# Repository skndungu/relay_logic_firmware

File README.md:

# Relay Logic Firmware
The repo contains all the firmware codes for the project and instructions on how to load them to the hardware
  <br/>

## What's fisrt needed
1) Set up the IDE, for this application you will need to down the Arduino ide [here](https://www.arduino.cc/en/software) if you don't have it already installed for your distributions
2) Once downloaded and proceed to the next instructions

## Download the Files :arrow_down_small:
3)  Download all the files on the `Code`:arrow_down_small: on this platform, In your downloads you will get the a folder :file_folder:  `relay_logic_firmware
-master` this will have all the codes and related libraries.
## Burning bootload to the MCU :fire:
## Note: DO THIS ON A WINDOWS OPERATING SYSTEM!!!
4) Do this on older version of arduino particularly version 1.6.0 grab the software [here](https://www.arduino.cc/en/Main/OldSoftwareReleases)
5) Once you have the setup to burn the bootloader please follow this tutorial [here](https://www.youtube.com/watch?v=Kh4iZb2YTT8&t=337s)
6) You need to have a functional Arduino Nano with you - just buy one locally as it's used in the process of bootloading
 
# Uploading the codes  :arrow_up:

You can buy the USBASP from here :link: [buy usbasp](https://aliexpress.ru/af/USBASP-USBISP-AVR-Programmer-USB.html?catId=0&d=y&aff_platform=portals-tool&initiative_id=SB_20201020044645&origin=n&sk=_9JHld5&aff_trace_key=4b1704d992da43b586041dfb7cd31d7e-1606574782769-00350-_9JHld5&SearchText=USBASP%2BUSBISP%2BAVR%2BProgrammer%2BUSB&terminal_id=351d58321dfa473cb106b58978d7c19c)
or here 
 :link: [buy usbasp](https://aliexpress.ru/item/32649685244.html?spm=a2g0o.productlist.0.0.22e26eaf2mIeLt&algo_pvid=b6506204-320d-4244-9d76-c7a1c32c5ee5&algo_expid=b6506204-320d-4244-9d76-c7a1c32c5ee5-16&btsid=0b8b036a16065747853274219e2939&ws_ab_test=searchweb0_0,searchweb201602_,searchweb201603_)

1) Insert the ISP programmer cable socket onto ISP header. ...
2) Open Arduino IDE software. ...
3) Next, call out the source code. ...
4) Select “USBasp” from the Tools > Programmer menu.
5) Select “Upload using Programmer” from the File menu.

<h3> upload the code snapshot </h3> see the screenshot

</img> 
You can also explore more from the following tutorial :link:[How to Use USBasp Programmer with Arduino Boards](https://www.youtube.com/watch?v=ToKerwRR-70)

## Debugging 
9) To see the serial data as sent or received from either of the boards we can use the FTDI programmer or any USB to TTL converter so that you can have access to a serial port. Check out the headers on the board for uart communications

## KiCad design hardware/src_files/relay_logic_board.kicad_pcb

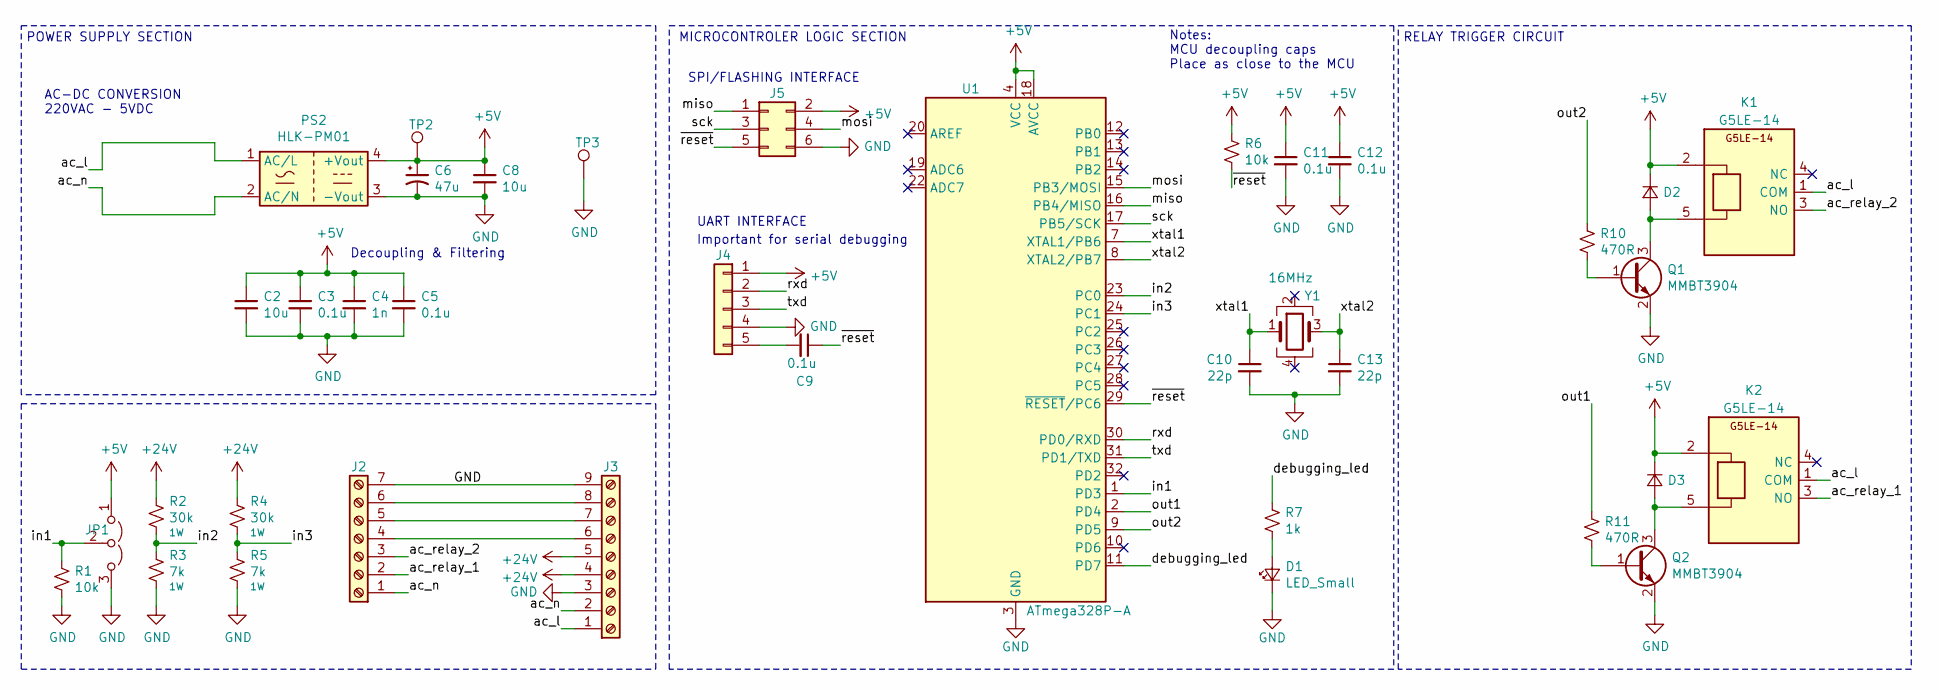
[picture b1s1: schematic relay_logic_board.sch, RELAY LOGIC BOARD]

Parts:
C2, C8: 10u; C_0603_1608Metric
C3, C5, C9, C11, C12: 0.1u; C_0603_1608Metric
C4: 1n; C_0603_1608Metric
C6: 47u; CP_Elec_4x5.3
C10, C13: 22p; C_0603_1608Metric
D1: LED_Small; LED_0603_1608Metric_Pad1.05x0.95mm_HandSolder
D2, D3: D_Small; D_SOD-123
J2: Screw_Terminal_01x07; TerminalBlock_4Ucon_1x07_P3.50mm_Horizontal
J3: Screw_Terminal_01x09; TerminalBlock_4Ucon_1x09_P3.50mm_Horizontal
J4: Conn_01x05; PinHeader_1x05_P2.54mm_Vertical
J5: Conn_02x03_Odd_Even; PinHeader_2x03_P2.54mm_Vertical
JP1: Jumper_3_Open; PinHeader_1x03_P2.54mm_Vertical
K1, K2: G5LE-14; Mfr# G5LE-14-DC5
PS2: HLK-PM01; Converter_ACDC_HiLink_HLK-PMxx
Q1, Q2: MMBT3904; SOT-23
R1, R6: 10k; R_0603_1608Metric
R2, R4: 30k; R_2512_6332Metric; Mfr# CR2512J30K0E04Z
R3, R5: 7k; R_2512_6332Metric; Mfr# AECR2512F1K00K9
R7: 1k; R_0603_1608Metric
R10, R11: 470R; R_0603_1608Metric
TP2, TP3: TestPoint; TestPoint_Pad_D0.9mm
U1: ATmega328P-A; TQFP-32_7x7mm_P0.8mm
Y1: 16MHz; Crystal_SMD_Abracon_ABM8G-4Pin_3.2x2.5mm

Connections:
+5V: C2.1, C3.1, C4.1, C5.1, C6.1, C8.1, C11.1, C12.1, D2.1 (K), D3.1 (K), J4.1, J5.2, JP1.1 (A), K1.2, K2.2, PS2.4 (+Vout), R6.2, TP2.1, U1.4 (VCC), U1.6 (VCC), U1.18 (AVCC)
+24V: J3.4, J3.5, R2.1, R4.1
/ac_l: J3.1, K1.1 (COM), K2.1 (COM), PS2.1 (AC/L)
/ac_n: J2.1, J3.2, PS2.2 (AC/N)
/ac_relay_1: J2.2, K2.3 (NO)
/ac_relay_2: J2.3, K1.3 (NO)
/debugging_led: R7.1, U1.11 (PD7)
/in1: JP1.2 (C), R1.2, U1.1 (PD3)
/in2: R2.2, R3.1, U1.23 (PC0)
/in3: R4.2, R5.1, U1.24 (PC1)
/miso: J5.1, U1.16 (PB4/MISO)
/mosi: J5.4, U1.15 (PB3/MOSI)
/out1: R11.1, U1.2 (PD4)
/out2: R10.1, U1.9 (PD5)
/rxd: J4.2, U1.30 (PD0/RXD)
/sck: J5.3, U1.17 (PB5/SCK)
/txd: J4.3, U1.31 (PD1/TXD)
/xtal1: C10.1, U1.7 (XTAL1/PB6), Y1.1
/xtal2: C13.1, U1.8 (XTAL2/PB7), Y1.3
/~reset: C9.1, J5.5, R6.1, U1.29 (~RESET~/PC6)
GND: C2.2, C3.2, C4.2, C5.2, C6.2, C8.2, C10.2, C11.2, C12.2, C13.2, D1.1 (K), J2.7, J3.3, J3.9, J4.4, J5.6, JP1.3 (B), PS2.3 (-Vout), Q1.2 (E), Q2.2 (E), R1.1, R3.2, R5.2, TP3.1, U1.3 (GND), U1.5 (GND), U1.21 (GND)
unnamed: C9.2, J4.5
unnamed: D1.2 (A), R7.2
unnamed: D2.2 (A), K1.5, Q1.3 (C)
unnamed: D3.2 (A), K2.5, Q2.3 (C)
unnamed: J2.4, J3.6
unnamed: J2.5, J3.7
unnamed: J2.6, J3.8
unnamed: Q1.1 (B), R10.2
unnamed: Q2.1 (B), R11.2

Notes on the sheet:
Notes: MCU decoupling caps Place as close to the MCU
UART INTERFACE
Important for serial debugging
SPI/FLASHING INTERFACE
MICROCONTROLER LOGIC SECTION
POWER SUPPLY SECTION
AC-DC CONVERSION 220VAC - 5VDC
Decoupling & Filtering
RELAY TRIGGER CIRCUIT

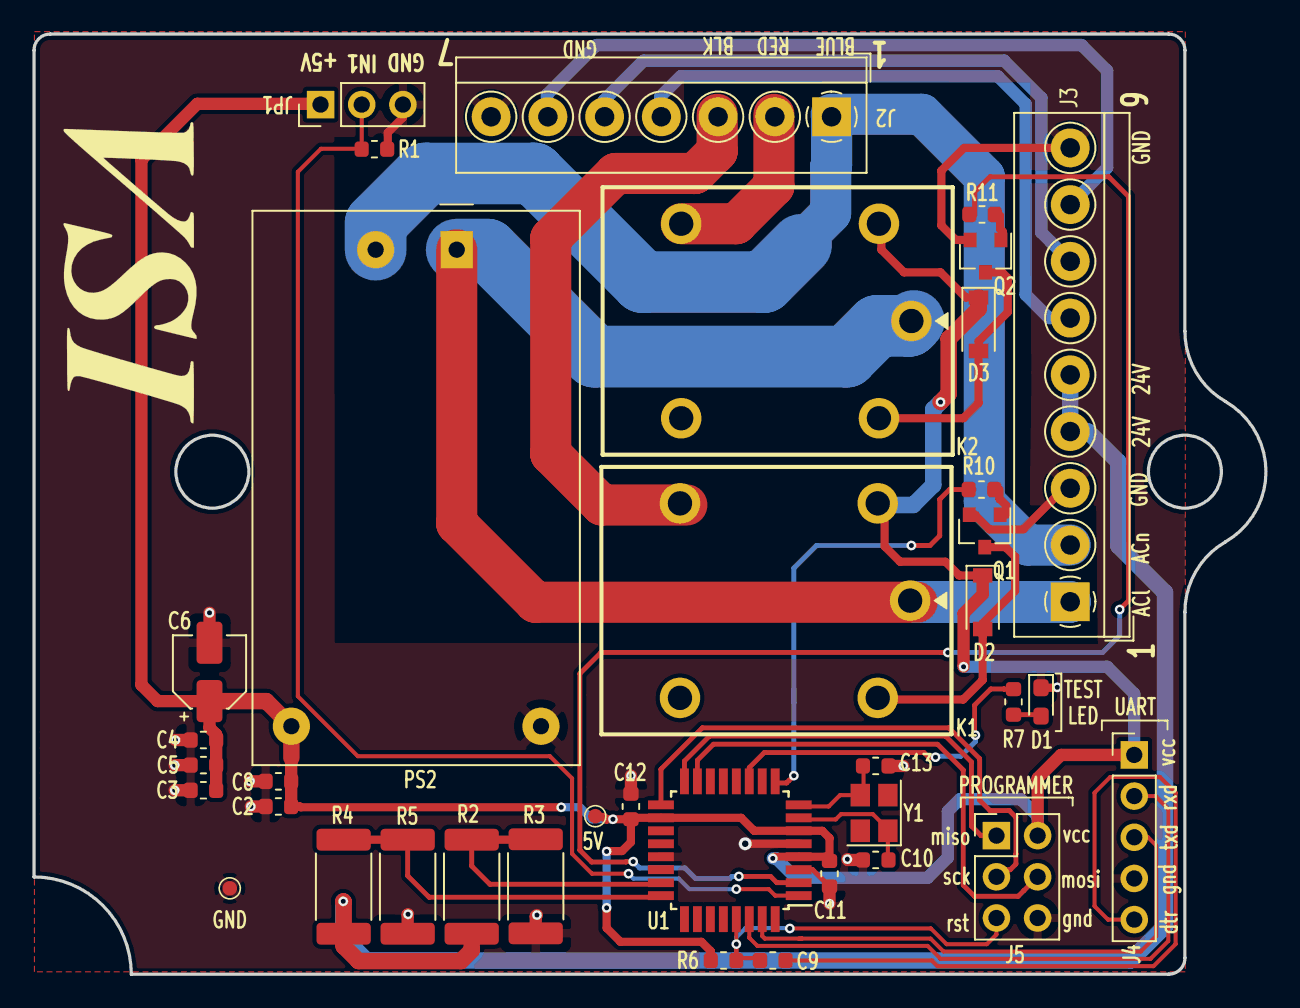
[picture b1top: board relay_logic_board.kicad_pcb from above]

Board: 2 copper layers, 76.0 x 58.0 mm, 37 parts (0 on the bottom side), 30 nets.

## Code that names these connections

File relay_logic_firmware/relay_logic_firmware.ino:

/*
 * TITLE: RELAY LOGIC FIRMWARE
 * 
 * AUTHOR: SIMON
 *
 * DATE: SEP, 23 2021
 * 
 */

#define in1 3  // input terminal
#define in2 A0 // input terminal
#define in3 A1 // input terminal
#define out1 4  // relay triggers
#define out2 5 // relay triggers

#define debugging_led 7 // led on the board for debugging 

int in1_state = 0;
int in2_state = 0;
int in3_state = 0;

boolean development = true;

void setup() {
  if(development){
  	  Serial.begin(9600);
  	  Serial.println("Relay Logic Test!");
  }
  pinMode(debugging_led, OUTPUT);
  pinMode(out1, OUTPUT);
  pinMode(out2, OUTPUT);
  pinMode(in1, INPUT);

  test_led();
}

void loop() {
 execute();
}

void take_reading(){
in1_state = digitalRead(in1);
in2_state = analogRead(in2);
in3_state = analogRead(in3);

if(in2_state > 400){ // takes an analog value if greater that 400 means we have an input voltage
	in2_state = 1;
} else{
	in2_state = 0;
}

if(in3_state > 400){
  in3_state = 1;
} else{
	in3_state = 0;
}

Serial.print("in1: ");
Serial.println(in1_state);
Serial.print("in2: ");
Serial.println(in2_state);
Serial.print("in3: ");
Serial.println(in3_state);

Serial.println("");

}

void execute(){
	if(in1 == 0 && in2 == 0 && in3 == 0){
		digitalWrite(out1, LOW);
		digitalWrite(out2, LOW);
	}
	if(in1 == 0 && in2 == 0 && in3 == 1){
		digitalWrite(out1, LOW);
		digitalWrite(out2, HIGH);
	}
	if(in1 == 0 && in2 == 1 && in3 == 0){
		digitalWrite(out1, HIGH);
		digitalWrite(out2, LOW);
	}
	if(in1 == 0 && in2 == 1 && in3 == 1){
		digitalWrite(out1, LOW);
		digitalWrite(out2, LOW);
	}
	if(in1 == 1 && in2 == 0 && in3 == 0){
		digitalWrite(out1, HIGH);
		digitalWrite(out2, LOW);
	}
	if(in1 == 1 && in2 == 0 && in3 == 1){
		digitalWrite(out1, HIGH);
		digitalWrite(out2, LOW);
	}
	if(in1 == 1 && in2 == 1 && in3 == 0){
		digitalWrite(out1, LOW);
		digitalWrite(out2, HIGH);
	}
	if(in1 == 1 && in2 == 1 && in3 == 1){
		digitalWrite(out1, LOW);
		digitalWrite(out2, LOW);
	}
}

void test_led(){
 digitalWrite(debugging_led, HIGH);
 delay(500);
 digitalWrite(debugging_led, LOW);
 delay(500);
}

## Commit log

2021-09-23 initial commit
    initial commit
2021-09-23 text file update
    text file update
2021-09-23 fimware v01 commit
    firmware v01 commit
2021-09-23 harware files
    pcb files
2021-09-23 hardware
    hardware files and description
2021-09-24 hardware files update, bom,gerbers&centroid files
    hardware files update, bom,gerbers&centroid files
